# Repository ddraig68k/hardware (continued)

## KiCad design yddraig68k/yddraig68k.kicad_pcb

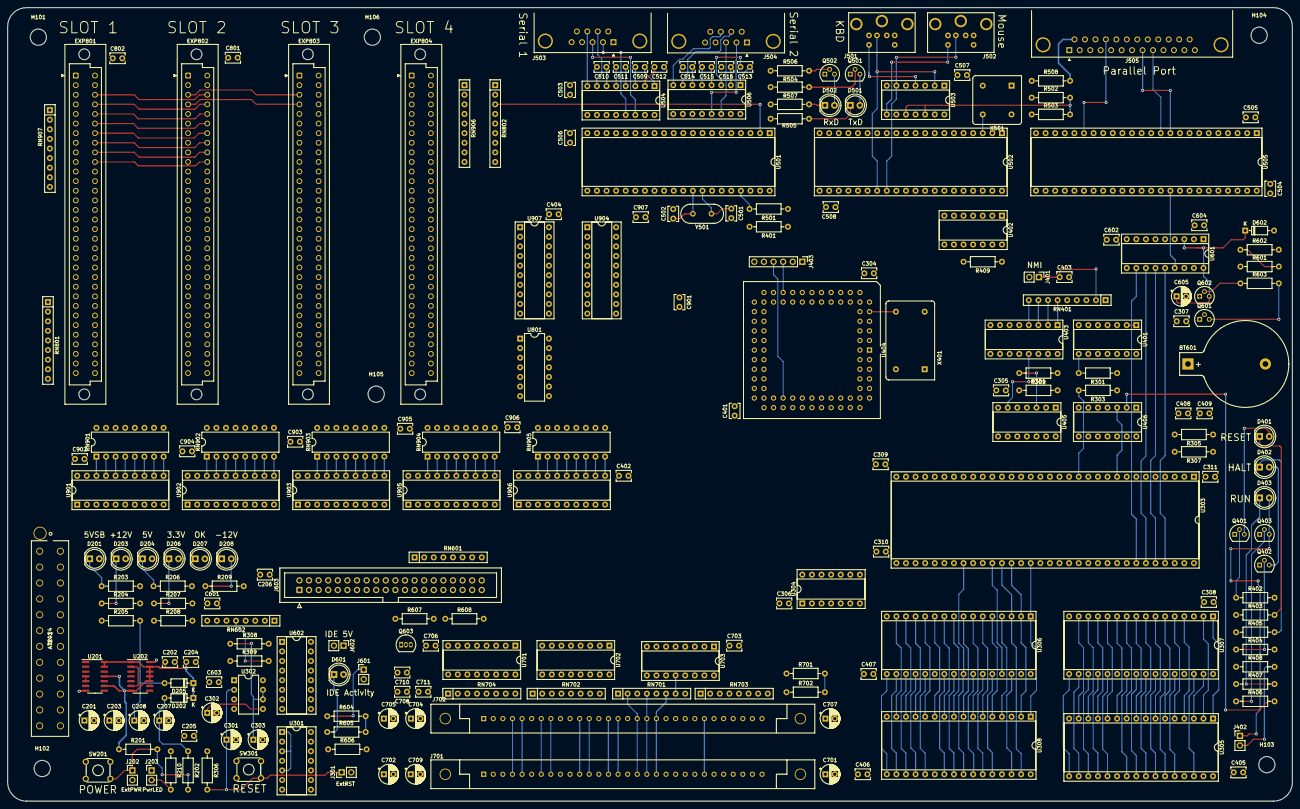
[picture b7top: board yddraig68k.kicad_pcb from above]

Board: 4 copper layers, 340.0 x 210.0 mm, 222 parts (0 on the bottom side), 370 nets.

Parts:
BT601: CR2032; BatteryHolder_Keystone_103_1x20mm
C201, C203, C701, C704, C707, C709: 47uF; CP_Radial_D5.0mm_P2.50mm
C202, C204, C205, C206, C304, C305, C306, C307, C308, C309, C310, C311, C401, C402, C403, C404, C405, C406, C407, C408, C409, C503, C504, C505, C506, C507, C508, C509, C510, C511, C512, C513, C514, C515, C516, C601, C602, C603, C604, C703, C706, C708, C710, C711, C801, C802, C901, C902, C903, C904, C905, C906, C907: 100nF; C_Disc_D3.8mm_W2.6mm_P2.50mm
C207: 1uF; CP_Radial_D5.0mm_P2.50mm
C208, C301, C605, C702, C705: 10uF; CP_Radial_D5.0mm_P2.50mm
C302, C303: 10nF; CP_Radial_D5.0mm_P2.50mm
C501: 10pF; C_Disc_D3.8mm_W2.6mm_P2.50mm
C502: 5pF; C_Disc_D3.8mm_W2.6mm_P2.50mm
D201, D203, D204, D206, D207, D208: LED; LED_D5.0mm
D202, D205, D602: 1N4148; D_DO-35_SOD27_P7.62mm_Horizontal
D401, D402: RED; LED_D5.0mm
D403: GREEN; LED_D5.0mm
D501, D502: Green; LED_D5.0mm
D601: Blue; LED_D5.0mm
EXP801, EXP802, EXP803, EXP804: D68K_64PIN_PCB; DIN41612_C_2x32_Female_Vertical_THT
H101, H102, H103, H104, H105, H106: MountingHole; MountingHole_4.3mm_M4
J201: ATX-24; 1-1775099-3
J202: ExtPWR; PinHeader_1x02_P2.54mm_Vertical
J203: PWRLED; PinHeader_1x02_P2.54mm_Vertical
J301: Conn_01x02; PinHeader_1x02_P2.54mm_Vertical
J401: NMI Reset; PinHeader_1x02_P2.54mm_Vertical
J402: Ext RUN LED; PinHeader_1x02_P2.54mm_Vertical
J403: Conn_01x06; PinHeader_1x06_P2.54mm_Vertical
J501: Keyboard; MINI-DIN-6-FULL-SHIELD
J502: Mouse; MINI-DIN-6-FULL-SHIELD
J503: Serial1; DSUB-9_Male_Horizontal_P2.77x2.84mm_EdgePinOffset4.94mm_Hou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
J504: Serial2; DSUB-9_Male_Horizontal_P2.77x2.84mm_EdgePinOffset4.94mm_Hou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
J505: Parallel; DSUB-25_Female_Horizontal_P2.77x2.84mm_EdgePinOffset7.70mm_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
J601: IDE LED; PinHeader_1x02_P2.54mm_Vertical
J602: IDE 5V; PinHeader_1x02_P2.54mm_Vertical
J603: IDE_Interface; IDC-Header_2x20_P2.54mm_Vertical
J701, J702: SIMM-30
Q401, Q402, Q403, Q501, Q502, Q602: 2N4403; TO-92
Q601: Q_NPN_EBC; TO-92
Q603: 2N7000; TO-92_Inline
R201, R205, R306, R502, R503, R607, R608: 10K; R_Axial_DIN0207_L6.3mm_D2.5mm_P10.16mm_Horizontal
R202: 470R; R_Axial_DIN0207_L6.3mm_D2.5mm_P10.16mm_Horizontal
R203, R206, R207, R208, R210, R604, R605: 330R; R_Axial_DIN0207_L6.3mm_D2.5mm_P10.16mm_Horizontal
R204, R209: 680R; R_Axial_DIN0207_L6.3mm_D2.5mm_P10.16mm_Horizontal
R301, R302, R303, R304, R305, R307, R309, R401, R409, R501, R601, R602, R603: 4K7; R_Axial_DIN0207_L6.3mm_D2.5mm_P10.16mm_Horizontal
R308: 38K; R_Axial_DIN0207_L6.3mm_D2.5mm_P10.16mm_Horizontal
R402, R404, R406, R508: 1K; R_Axial_DIN0207_L6.3mm_D2.5mm_P10.16mm_Horizontal
R403, R405, R407, R408, R504, R505, R506, R507: 150R; R_Axial_DIN0207_L6.3mm_D2.5mm_P10.16mm_Horizontal
R606: 1M; R_Axial_DIN0207_L6.3mm_D2.5mm_P10.16mm_Horizontal
R701, R702: 22R; R_Axial_DIN0207_L6.3mm_D2.5mm_P10.16mm_Horizontal
RN401, RN801, RN802, RN906, RN907: 10K; R_Array_SIP9
RN601, RN602, RN701, RN702, RN703, RN704: 22R; R_Array_SIP8
RN901, RN902, RN903, RN904, RN905: 22R; DIP-16_W7.62mm
SW201, SW301: SW_DPST; SW_TH_Tactile_Omron_B3F-10xx
U201, U202: 74HCT74; SO-14_3.9x8.65mm_P1.27mm
U301, U503: 74LS06; DIP-14_W7.62mm_Socket
U302: NE555P; DIP-8_W7.62mm
U303: 68000D; DIP-64_W22.86mm_Socket
U304: 74LS32; DIP-14_W7.62mm_Socket
U305, U306: SST39SF040; DIP-32_W15.24mm_Socket
U307, U308: AS6C4008-55PCN; DIP-32_W15.24mm_Socket
U401: 74HC164; DIP-14_W7.62mm_Socket
U402, U405: 74LS08; DIP-14_W7.62mm_Socket
U403: 74LS148; DIP-16_W7.62mm_Socket
U404: XC95108PC84; PLCC-84_THT-Socket
U406: 74LS04; DIP-14_W7.62mm_Socket
U501: 68681; DIP-40_W15.24mm_Socket
U502: VT82C42; DIP-40_W15.24mm_Socket
U504, U506: MAX202; DIP-16_W7.62mm_Socket
U505: 68230; DIP-48_W15.24mm_Socket
U601: RTC-72421; DIP-18_W7.62mm_Socket
U602: 74LS139; DIP-16_W7.62mm_Socket
U701, U702, U703: 74LS157; DIP-16_W7.62mm_Socket
U801: 74LS21; DIP-14_W7.62mm
U901, U902, U903: 74LS541; DIP-20_W7.62mm_Socket
U904, U905, U906, U907: 74LS245; DIP-20_W7.62mm_Socket
X401: 40MHz; Oscillator_DIP-14
X501: CXO_DIP8; Oscillator_DIP-8
Y501: 3.6864MHz; Crystal_HC18-U_Vertical

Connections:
+3V3: D206.2, EXP801.C30, EXP802.C30, EXP803.C30, EXP804.C30, J201.1, J201.2, J201.12, J201.13
+5V: C201.1, C203.1, C205.1, C206.1, C304.1, C305.1, C306.1, C307.1, C308.1, C309.1, C310.1, C311.1, C401.1, C402.1, C404.1, C405.1, C406.1, C407.1, C408.1, C409.1, C503.1, C504.1, C505.1, C506.1, C507.1, C508.1, C512.1, C516.2, C601.1, C602.1, C603.1, C604.1, C701.1, C702.1, C703.1, C704.1, C705.1, C706.1, C707.1, C708.1, C709.1, C710.1, C711.1, C801.1, C802.1, C901.1, C902.1, C903.1, C904.1, C905.1, C906.1, C907.1, D204.2, D601.2, EXP801.A1, EXP801.A24, EXP801.C1, EXP802.A1, EXP802.A24, EXP802.C1, EXP803.A1, EXP803.A24, EXP803.C1, EXP804.A1, EXP804.A24, EXP804.C1, J201.4, J201.6, J201.21, J201.22, J201.23, J203.1, J403.1, J501.4, J502.4, J601.2, J602.2, J701.1, J701.30, J702.1, J702.30, Q401.1, Q402.1, Q403.1, Q501.1, Q502.1, Q602.1, R301.1, R302.1, R303.1, R304.1, R305.1, R306.1, R307.1, R308.1, R309.1, R401.1, R409.1, R501.1, R502.1, R503.1, R508.1, R601.1, R606.1, R608.2, RN401.1, RN801.1, RN802.1, U301.9, U301.11, U301.13, U301.14, U302.4, U302.8, U303.14, U303.49, U304.14, U305.32, U306.32, U307.32, U308.32, U401.14, U402.14, U403.16, U404.22, U404.38, U404.64, U404.73, U404.78, U405.14, U406.14, U501.40, U502.5, U502.25, U502.26, U502.40, U503.14, U504.16, U505.12, U506.16, U602.13, U602.14, U602.15, U602.16, U701.16, U702.16, U703.16, U801.14, U901.20, U902.20, U903.20, U904.20, U905.20, U906.20, U907.20, X401.14, X501.1, X501.8
+5V_SB: C202.1, C204.1, D201.2, D202.1, D205.1, EXP801.C2, EXP802.C2, EXP803.C2, EXP804.C2, J201.9, R201.1, R205.1, U201.9, U201.11, U201.13, U201.14, U202.1, U202.7, U202.10, U202.11, U202.12, U202.13
+12V: D203.2, EXP801.A31, EXP801.C31, EXP802.A31, EXP802.C31, EXP803.A31, EXP803.C31, EXP804.A31, EXP804.C31, J201.10, J201.11
-12V: D208.1, EXP801.A30, EXP802.A30, EXP803.A30, EXP804.A30, J201.14
/CPU, RAM and ROM/A1: RN601.1, U303.29, U305.12, U306.12, U307.12, U308.12, U501.1, U502.9, U505.29, U601.4, U701.2, U901.2
/CPU, RAM and ROM/A2: RN601.3, U303.30, U305.11, U306.11, U307.11, U308.11, U501.3, U505.28, U601.5, U701.3, U901.3
/CPU, RAM and ROM/A3: RN601.5, U303.31, U305.10, U306.10, U307.10, U308.10, U501.5, U505.27, U601.6, U701.5, U901.4
/CPU, RAM and ROM/A4: U303.32, U305.9, U306.9, U307.9, U308.9, U501.6, U505.26, U601.7, U701.6, U901.5
/CPU, RAM and ROM/A5: U303.33, U305.8, U306.8, U307.8, U308.8, U505.25, U701.11, U901.6
/CPU, RAM and ROM/A6: U303.34, U305.7, U306.7, U307.7, U308.7, U701.10, U901.7
/CPU, RAM and ROM/A7: U303.35, U305.6, U306.6, U307.6, U308.6, U602.2, U701.14, U901.8
/CPU, RAM and ROM/A8: U303.36, U305.5, U306.5, U307.5, U308.5, U404.71, U701.13, U901.9
/CPU, RAM and ROM/A9: U303.37, U305.27, U306.27, U307.27, U308.27, U404.72, U702.2, U902.2
/CPU, RAM and ROM/A10: U303.38, U305.26, U306.26, U307.26, U308.26, U404.74, U702.3, U902.3
/CPU, RAM and ROM/A11: U303.39, U305.23, U306.23, U307.23, U308.23, U404.75, U702.5, U902.4
/CPU, RAM and ROM/A12: U303.40, U305.25, U306.25, U307.25, U308.25, U404.76, U702.6, U902.5
/CPU, RAM and ROM/A13: U303.41, U305.4, U306.4, U307.4, U308.4, U404.77, U702.11, U902.6
/CPU, RAM and ROM/A14: U303.42, U305.28, U306.28, U307.28, U308.28, U404.79, U702.10, U902.7
/CPU, RAM and ROM/A15: U303.43, U305.29, U306.29, U307.3, U308.3, U404.80, U702.14, U902.8
/CPU, RAM and ROM/A16: U303.44, U305.3, U306.3, U307.31, U308.31, U404.81, U702.13, U902.9
/CPU, RAM and ROM/A17: U303.45, U305.2, U306.2, U307.2, U308.2, U404.82, U703.2, U903.2
/CPU, RAM and ROM/A18: U303.46, U305.30, U306.30, U307.30, U308.30, U404.83, U703.3, U903.3
/CPU, RAM and ROM/A19: U303.47, U305.1, U306.1, U307.1, U308.1, U404.84, U703.5, U903.4
/CPU, RAM and ROM/A20: U303.48, U404.57, U703.6
/CPU, RAM and ROM/A21: U303.50, U404.58, U703.11
/CPU, RAM and ROM/A22: U303.51, U404.61, U703.10
/CPU, RAM and ROM/A23: U303.52, U404.62, U703.14
/CPU, RAM and ROM/CLK10: U303.15, U404.10, U505.40, U904.11
/CPU, RAM and ROM/D0: J603.4, J702.3, U303.5, U305.13, U307.13, U905.2
/CPU, RAM and ROM/D1: J603.6, J702.6, U303.4, U305.14, U307.14, U905.3
/CPU, RAM and ROM/D2: J603.8, J702.10, U303.3, U305.15, U307.15, U905.4
/CPU, RAM and ROM/D3: J603.10, J702.13, U303.2, U305.17, U307.17, U905.5
/CPU, RAM and ROM/D4: J603.12, J702.16, U303.1, U305.18, U307.18, U905.6
/CPU, RAM and ROM/D5: J603.14, J702.20, U303.64, U305.19, U307.19, U905.7
/CPU, RAM and ROM/D6: J603.16, J702.23, U303.63, U305.20, U307.20, U905.8
/CPU, RAM and ROM/D7: J603.18, J702.25, U303.62, U305.21, U307.21, U905.9
/CPU, RAM and ROM/D8: J603.17, J701.3, U303.61, U306.13, U308.13, U501.25, U502.12, U505.44, U601.14, U906.2
/CPU, RAM and ROM/D9: J603.15, J701.6, U303.60, U306.14, U308.14, U501.16, U502.13, U505.45, U601.13, U906.3
/CPU, RAM and ROM/D10: J603.13, J701.10, U303.59, U306.15, U308.15, U501.24, U502.14, U505.46, U601.12, U906.4
/CPU, RAM and ROM/D11: J603.11, J701.13, U303.58, U306.17, U308.17, U501.17, U502.15, U505.47, U601.11, U906.5
/CPU, RAM and ROM/D12: J603.9, J701.16, U303.57, U306.18, U308.18, U501.23, U502.16, U505.48, U906.6
/CPU, RAM and ROM/D13: J603.7, J701.20, U303.56, U306.19, U308.19, U501.18, U502.17, U505.1, U906.7
/CPU, RAM and ROM/D14: J603.5, J701.23, U303.55, U306.20, U308.20, U501.22, U502.18, U505.2, U906.8
/CPU, RAM and ROM/D15: J603.3, J701.25, U303.54, U306.21, U308.21, U501.19, U502.19, U505.3, U906.9
/CPU, RAM and ROM/E: U303.20, U904.12
/CPU, RAM and ROM/FC0: U303.28, U404.11
/CPU, RAM and ROM/FC1: U303.27, U404.12
/CPU, RAM and ROM/FC2: U303.26, U404.13
/CPU, RAM and ROM/RD~WR: U303.9, U305.31, U306.31, U307.29, U308.29, U404.66, U406.3, U501.8, U502.10, U505.43, U601.10, U904.15
/CPU, RAM and ROM/RESET: U301.1, U301.3, U301.5, U302.3
/CPU, RAM and ROM/~AS: R301.2, U303.6, U401.8, U404.63, U901.1, U902.1, U903.1, U904.14
/CPU, RAM and ROM/~BERR: U303.22, U402.8
/CPU, RAM and ROM/~CPU_RESET: R307.2, R402.2, U301.6, U303.18, U402.13
/CPU, RAM and ROM/~CS_ROM: U304.2, U304.10, U404.7
/CPU, RAM and ROM/~CS_SRAM: U304.5, U304.13, U404.6
/CPU, RAM and ROM/~DTACK: U303.10, U402.6
/CPU, RAM and ROM/~HALT: R305.2, R404.2, U301.4, U303.17, U402.12
/CPU, RAM and ROM/~IPL0: U303.25, U403.9
/CPU, RAM and ROM/~IPL1: U303.24, U403.7
/CPU, RAM and ROM/~IPL2: U303.23, U403.6
/CPU, RAM and ROM/~LDS: U303.8, U304.1, U304.4, U404.65, U904.17
/CPU, RAM and ROM/~RD~WR: U305.24, U306.24, U307.24, U308.24, U406.4, U502.8, U601.8, U905.1, U906.1
/CPU, RAM and ROM/~RESET: R309.2, RN602.5, U301.2, U401.9, U404.48, U501.34, U502.4, U505.39, U601.15, U904.18
/CPU, RAM and ROM/~UDS: U303.7, U304.9, U304.12, U404.44, U904.16
/CPU, RAM and ROM/~VMA: U303.19, U904.13
/CPU, RAM and ROM/~VPA: R302.2, U303.21, U405.3
/DRAM Interface/DRAM_MUX: U404.50, U701.1, U702.1, U703.1
/DRAM Interface/~CAS0: RN703.1, U404.55
/DRAM Interface/~CAS1: RN703.3, U404.56
/DRAM Interface/~DRAM_WE: R701.2, R702.2, U404.51
/DRAM Interface/~RAS0: RN703.5, U404.53
/DRAM Interface/~RAS1: RN703.7, U404.45
/Decode and Logic/BOOTROM: U401.6, U404.1
/Decode and Logic/~CPLD_BERR: U402.9, U404.69
/Decode and Logic/~CPLD_VPA: U404.39, U405.1
/Decode and Logic/~CS_DUART: U404.15, U501.35
/Decode and Logic/~CS_EXTDATA1: U404.23, U907.14
/Decode and Logic/~CS_EXTDATA2: U404.24, U907.13
/Decode and Logic/~CS_EXTDATA3: U404.25, U907.12
/Decode and Logic/~CS_EXTDATA4: U404.26, U907.11
/Decode and Logic/~CS_EXTREG1: U404.31, U907.18
/Decode and Logic/~CS_EXTREG2: U404.32, U907.17
/Decode and Logic/~CS_EXTREG3: U404.33, U907.16
/Decode and Logic/~CS_EXTREG4: U404.34, U907.15
/Decode and Logic/~CS_IDE: U404.35, U602.1
/Decode and Logic/~CS_KBD: U404.5, U502.6
/Decode and Logic/~CS_PIT: U404.4, U505.41
/Decode and Logic/~CS_RTC: U404.20, U601.2
/Decode and Logic/~DATCK_68K: R409.2, U402.1, U501.9, U505.42
/Decode and Logic/~DATCK_EXT: U402.5, U801.8
/Decode and Logic/~DTACK_CPLD: U402.2, U404.2
/Decode and Logic/~EXTINT1: EXP801.A28, RN401.3, U403.11
/Decode and Logic/~EXTINT2: EXP802.A28, RN401.8, U403.3
/Decode and Logic/~EXTINT3: EXP803.A28, RN401.9, U403.4
/Decode and Logic/~EXT_BERR: U402.10, U801.6
/Decode and Logic/~EXT_LDS: U404.68, U905.19
/Decode and Logic/~EXT_UDS: U404.70, U906.19
/Decode and Logic/~EXT_VPA: EXP801.A23, EXP802.A23, EXP803.A23, EXP804.A23, RN802.6, U405.2
/Decode and Logic/~IDE_RD: RN602.3, U404.18
/Decode and Logic/~IDE_WR: RN602.1, U404.17
/Decode and Logic/~INT_DUART: RN401.6, U403.1, U501.21
/Decode and Logic/~INT_IDE: Q603.3, R606.2, RN401.4, U403.12
/Decode and Logic/~INT_PIT0: U405.4, U505.33
/Decode and Logic/~INT_PIT1: U405.5, U505.35
/Decode and Logic/~INT_PS2: R502.2, R503.2, RN401.7, U403.2, U503.10, U503.12
/Decode and Logic/~RUN: R406.2, U406.2
/Expansion Bus/BA1: EXP801.A12, EXP802.A12, EXP803.A12, EXP804.A12, RN901.16
/Expansion Bus/BA2: EXP801.C12, EXP802.C12, EXP803.C12, EXP804.C12, RN901.15
/Expansion Bus/BA3: EXP801.A13, EXP802.A13, EXP803.A13, EXP804.A13, RN901.14
/Expansion Bus/BA4: EXP801.C13, EXP802.C13, EXP803.C13, EXP804.C13, RN901.13
/Expansion Bus/BA5: EXP801.A14, EXP802.A14, EXP803.A14, EXP804.A14, RN901.12
/Expansion Bus/BA6: EXP801.C14, EXP802.C14, EXP803.C14, EXP804.C14, RN901.11
/Expansion Bus/BA7: EXP801.A15, EXP802.A15, EXP803.A15, EXP804.A15, RN901.10
/Expansion Bus/BA8: EXP801.C15, EXP802.C15, EXP803.C15, EXP804.C15, RN901.9
/Expansion Bus/BA9: EXP801.A16, EXP802.A16, EXP803.A16, EXP804.A16, RN902.16
/Expansion Bus/BA10: EXP801.C16, EXP802.C16, EXP803.C16, EXP804.C16, RN902.15
/Expansion Bus/BA11: EXP801.A17, EXP802.A17, EXP803.A17, EXP804.A17, RN902.14
/Expansion Bus/BA12: EXP801.C17, EXP802.C17, EXP803.C17, EXP804.C17, RN902.13
/Expansion Bus/BA13: EXP801.A18, EXP802.A18, EXP803.A18, EXP804.A18, RN902.12
/Expansion Bus/BA14: EXP801.C18, EXP802.C18, EXP803.C18, EXP804.C18, RN902.11
/Expansion Bus/BA15: EXP801.A19, EXP802.A19, EXP803.A19, EXP804.A19, RN902.10
/Expansion Bus/BA16: EXP801.C19, EXP802.C19, EXP803.C19, EXP804.C19, RN902.9
/Expansion Bus/BA17: EXP801.A20, EXP802.A20, EXP803.A20, EXP804.A20, RN903.16
/Expansion Bus/BA18: EXP801.C20, EXP802.C20, EXP803.C20, EXP804.C20, RN903.15
/Expansion Bus/BA19: EXP801.A21, EXP802.A21, EXP803.A21, EXP804.A21, RN903.14
/Expansion Bus/BCLK10: EXP801.C23, EXP802.C23, EXP803.C23, EXP804.C23, U904.9
/Expansion Bus/BD0: EXP801.A3, EXP802.A3, EXP803.A3, EXP804.A3, RN904.16, RN906.2
/Expansion Bus/BD1: EXP801.C3, EXP802.C3, EXP803.C3, EXP804.C3, RN904.15, RN906.3
/Expansion Bus/BD2: EXP801.A4, EXP802.A4, EXP803.A4, EXP804.A4, RN904.14, RN906.4
/Expansion Bus/BD3: EXP801.C4, EXP802.C4, EXP803.C4, EXP804.C4, RN904.13, RN906.5
/Expansion Bus/BD4: EXP801.A5, EXP802.A5, EXP803.A5, EXP804.A5, RN904.12, RN906.6
/Expansion Bus/BD5: EXP801.C5, EXP802.C5, EXP803.C5, EXP804.C5, RN904.11, RN906.7
/Expansion Bus/BD6: EXP801.A6, EXP802.A6, EXP803.A6, EXP804.A6, RN904.10, RN906.8
/Expansion Bus/BD7: EXP801.C6, EXP802.C6, EXP803.C6, EXP804.C6, RN904.9, RN906.9
/Expansion Bus/BD8: EXP801.A7, EXP802.A7, EXP803.A7, EXP804.A7, RN905.16, RN907.2
/Expansion Bus/BD9: EXP801.C7, EXP802.C7, EXP803.C7, EXP804.C7, RN905.15, RN907.3
/Expansion Bus/BD10: EXP801.A8, EXP802.A8, EXP803.A8, EXP804.A8, RN905.14, RN907.4
/Expansion Bus/BD11: EXP801.C8, EXP802.C8, EXP803.C8, EXP804.C8, RN905.13, RN907.5
/Expansion Bus/BD12: EXP801.A9, EXP802.A9, EXP803.A9, EXP804.A9, RN905.12, RN907.6
/Expansion Bus/BD13: EXP801.C9, EXP802.C9, EXP803.C9, EXP804.C9, RN905.11, RN907.7
/Expansion Bus/BD14: EXP801.A10, EXP802.A10, EXP803.A10, EXP804.A10, RN905.10, RN907.8
/Expansion Bus/BD15: EXP801.C10, EXP802.C10, EXP803.C10, EXP804.C10, RN905.9, RN907.9
/Expansion Bus/BE: EXP801.C21, EXP802.C21, EXP803.C21, EXP804.C21, U904.8
/Expansion Bus/BRD~WR: EXP801.A26, EXP802.A26, EXP803.A26, EXP804.A26, U904.5
/Expansion Bus/~BAS: EXP801.A22, EXP802.A22, EXP803.A22, EXP804.A22, U904.6
/Expansion Bus/~BCS_EXTDATA1: EXP801.C27, U907.6
/Expansion Bus/~BCS_EXTDATA2: EXP802.C27, U907.7
/Expansion Bus/~BCS_EXTDATA3: EXP803.C27, U907.8
/Expansion Bus/~BCS_EXTDATA4: EXP804.C27, U907.9
/Expansion Bus/~BCS_EXTREG1: EXP801.A27, U907.2
/Expansion Bus/~BCS_EXTREG2: EXP802.A27, U907.3
/Expansion Bus/~BCS_EXTREG3: EXP803.A27, U907.4
/Expansion Bus/~BCS_EXTREG4: EXP804.A27, U907.5
/Expansion Bus/~BLDS: EXP801.A25, EXP802.A25, EXP803.A25, EXP804.A25, U904.3
/Expansion Bus/~BRESET: EXP801.C26, EXP802.C26, EXP803.C26, EXP804.C26, U904.2
/Expansion Bus/~BUDS: EXP801.C25, EXP802.C25, EXP803.C25, EXP804.C25, U904.4
/Expansion Bus/~BVMA: EXP801.C22, EXP802.C22, EXP803.C22, EXP804.C22, U904.7
/Expansion Bus/~DTACK_EXT1: EXP801.C28, RN801.5, U801.9
/Expansion Bus/~DTACK_EXT2: EXP802.C28, RN801.4, U801.10
/Expansion Bus/~DTACK_EXT3: EXP803.C28, RN801.3, U801.12
/Expansion Bus/~DTACK_EXT4: EXP804.A28, RN801.2, U801.13
/Expansion Bus/~EXT_BERR1: EXP801.A29, RN801.9, U801.1
/Expansion Bus/~EXT_BERR2: EXP802.A29, RN801.8, U801.2
/Expansion Bus/~EXT_BERR3: EXP803.A29, RN801.7, U801.4
/Expansion Bus/~EXT_BERR4: EXP804.A29, RN801.6, U801.5
/Expansion Bus/~EXT_PD1: EXP801.C29, RN802.2, U501.36
/Expansion Bus/~EXT_PD2: EXP802.C29, RN802.3, U501.2
/Expansion Bus/~EXT_PD3: EXP803.C29, RN802.4, U501.39
/Expansion Bus/~EXT_PD4: EXP804.C29, RN802.5, U501.38
/IDE Interface/ACTIVE: J603.39, R604.2, R605.2
/IDE Interface/IRQ: J603.31, Q603.2
/Peripherals/PPACK: J505.10, U505.13
/Peripherals/PPBUSY: J505.11, U505.17
/Peripherals/PPERROR: J505.15, U505.15
/Peripherals/PPINIT: J505.16, U505.16
/Peripherals/PPPAPER: J505.12, U505.18
/Peripherals/PPSELECT: J505.17, U505.19
/Peripherals/PPSTROBE: J505.1, U505.14
/Peripherals/RXDA: R506.2, U501.31, U504.12
/Peripherals/TXDA: R504.2, U501.30, U504.11
/Power/PWR_OK: D207.2, J201.8
/Power/~PWR_ON: J201.16, U202.5
GND: BT601.2, C201.2, C202.2, C203.2, C204.2, C205.2, C206.2, C207.2, C208.2, C301.2, C302.2, C303.2, C304.2, C305.2, C306.2, C307.2, C308.2, C309.2, C310.2, C311.2, C401.2, C402.2, C403.2, C404.2, C405.2, C406.2, C407.2, C408.2, C409.2, C501.2, C502.2, C503.2, C504.2, C505.2, C506.2, C507.2, C508.2, C510.2, C514.2, C601.2, C602.2, C603.2, C604.2, C605.2, C701.2, C702.2, C703.2, C704.2, C705.2, C706.2, C707.2, C708.2, C709.2, C710.2, C711.2, C801.2, C802.2, C901.2, C902.2, C903.2, C904.2, C905.2, C906.2, C907.2, EXP801.A2, EXP801.A11, EXP801.A32, EXP801.C11, EXP801.C24, EXP801.C32, EXP802.A2, EXP802.A11, EXP802.A32, EXP802.C11, EXP802.C24, EXP802.C32, EXP803.A2, EXP803.A11, EXP803.A32, EXP803.C11, EXP803.C24, EXP803.C32, EXP804.A2, EXP804.A11, EXP804.A32, EXP804.C11, EXP804.C24, EXP804.C32, J201.3, J201.5, J201.7, J201.15, J201.17, J201.18, J201.19, J201.24, J202.2, J301.2, J401.2, J403.6, J501.3, J501.7, J502.3, J502.7, J503.0, J503.5, J504.0, J504.5, J505.0, J505.18, J505.19, J505.20, J505.21, J505.22, J505.23, J505.24, J505.25, J603.2, J603.19, J603.22, J603.24, J603.26, J603.28, J603.30, J603.40, J701.9, J701.22, J702.9, J702.22, Q601.1, Q603.1, R203.2, R204.2, R206.2, R207.2, R208.2, R209.2, R210.2, R403.1, R405.1, R407.1, R408.1, R505.2, R507.2, R602.2, R607.2, RN906.1, RN907.1, SW201.1, SW201.3, SW301.1, SW301.3, U201.7, U202.14, U301.7, U302.1, U303.16, U303.53, U304.7, U305.16, U306.16, U307.16, U308.16, U401.7, U402.7, U403.5, U403.8, U404.8, U404.16, U404.27, U404.42, U404.49, U404.60, U405.7, U405.9, U405.10, U405.12, U405.13, U406.5, U406.7, U406.9, U406.11, U406.13, U501.20, U502.2, U502.7, U502.20, U503.7, U504.15, U505.38, U506.15, U601.9, U602.3, U602.8, U701.8, U701.15, U702.8, U702.15, U703.8, U703.13, U703.15, U801.7, U901.10, U901.19, U902.10, U902.19, U903.5, U903.6, U903.7, U903.8, U903.9, U903.10, U903.19, U904.1, U904.10, U904.19, U905.10, U906.10, U907.1, U907.10, U907.19, X401.7, X501.4
unnamed: BT601.1, D602.2
unnamed: C207.1, D202.2, R202.1, U201.1
unnamed: C208.1, D205.2, R205.2, U201.3
unnamed: C301.1, J301.1, R306.2, SW301.2, SW301.4, U302.2
unnamed: C302.1, U302.5
unnamed: C303.1, R308.2, U302.6, U302.7
unnamed: C403.1, J401.1, RN401.2, U403.10
unnamed: C501.1, U501.33, Y501.1
unnamed: C502.1, U501.32, Y501.2
unnamed: C509.1, U504.1
unnamed: C509.2, U504.3
unnamed: C510.1, U504.6
unnamed: C511.1, U504.4
unnamed: C511.2, U504.5
unnamed: C512.2, U504.2
unnamed: C513.1, U506.1
unnamed: C513.2, U506.3
unnamed: C514.1, U506.6
unnamed: C515.1, U506.4
unnamed: C515.2, U506.5
unnamed: C516.1, U506.2
unnamed: C605.1, D602.1, Q602.3, U601.3, U601.18
unnamed: D201.1, R203.1
unnamed: D203.1, R204.1
unnamed: D204.1, R206.1
unnamed: D206.1, R207.1
unnamed: D207.1, R208.1
unnamed: D208.2, R209.1
unnamed: D401.1, R403.2
unnamed: D401.2, Q401.3
unnamed: D402.1, R405.2
unnamed: D402.2, Q402.3
unnamed: D403.1, R407.2
unnamed: D403.2, J402.1, Q403.3
unnamed: D501.1, R505.1
unnamed: D501.2, Q501.3
unnamed: D502.1, R507.1
unnamed: D502.2, Q502.3
unnamed: D601.1, R605.1
unnamed: J202.1, R201.2, R202.2, SW201.2, SW201.4
unnamed: J203.2, R210.1
unnamed: J402.2, R408.2
unnamed: J403.2, U404.30
unnamed: J403.3, U404.28
unnamed: J403.4, U404.59
unnamed: J403.5, U404.29
unnamed: J501.1, U502.27, U503.2
unnamed: J501.5, U502.1, U503.4
unnamed: J502.1, U502.28, U503.6
unnamed: J502.5, U502.39, U503.8
unnamed: J503.2, U504.13
unnamed: J503.3, U504.14
unnamed: J503.7, U504.7
unnamed: J503.8, U504.8
unnamed: J504.2, U506.13
unnamed: J504.3, U506.14
unnamed: J504.7, U506.7
unnamed: J504.8, U506.8
unnamed: J505.2, U505.4
unnamed: J505.3, U505.5
unnamed: J505.4, U505.6
unnamed: J505.5, U505.7
unnamed: J505.6, U505.8
unnamed: J505.7, U505.9
unnamed: J505.8, U505.10
unnamed: J505.9, U505.11
unnamed: J505.14, R508.2
unnamed: J601.1, R604.1
unnamed: J602.1, J603.20
unnamed: J603.1, RN602.6
unnamed: J603.21, R607.1
unnamed: J603.23, RN602.2
unnamed: J603.25, RN602.4
unnamed: J603.29, R608.1
unnamed: J603.33, RN601.4
unnamed: J603.35, RN601.2
unnamed: J603.36, RN601.6
unnamed: J603.37, U602.4
unnamed: J603.38, U602.5
unnamed: J701.2, RN703.2
unnamed: J701.4, J702.4, RN704.2
unnamed: J701.5, J702.5, RN704.4
unnamed: J701.7, J702.7, RN704.6
unnamed: J701.8, J702.8, RN704.8
unnamed: J701.11, J702.11, RN702.2
unnamed: J701.12, J702.12, RN702.4
unnamed: J701.14, J702.14, RN702.6
unnamed: J701.15, J702.15, RN702.8
unnamed: J701.17, J702.17, RN701.2
unnamed: J701.18, J702.18, RN701.4
unnamed: J701.19, J702.19, RN701.6
unnamed: J701.21, R701.1
unnamed: J701.24, J702.24, RN701.8
unnamed: J701.27, RN703.6
unnamed: J702.2, RN703.4
unnamed: J702.21, R702.1
unnamed: J702.27, RN703.8
unnamed: Q401.2, R402.1
unnamed: Q402.2, R404.1
unnamed: Q403.2, R406.1
unnamed: Q501.2, R504.1
unnamed: Q502.2, R506.1
unnamed: Q601.2, R601.2, R602.1
unnamed: Q601.3, R603.2
unnamed: Q602.2, R603.1
unnamed: R303.2, U303.13
unnamed: R304.2, U303.12
unnamed: R401.2, U401.1, U401.2
unnamed: R501.2, U501.37
unnamed: RN401.5, U403.13, U405.6
unnamed: RN701.1, U703.4
unnamed: RN701.3, U703.7
unnamed: RN701.5, U703.9
unnamed: RN701.7, U703.12
unnamed: RN702.1, U702.4
unnamed: RN702.3, U702.7
unnamed: RN702.5, U702.9
unnamed: RN702.7, U702.12
unnamed: RN704.1, U701.4
unnamed: RN704.3, U701.7
unnamed: RN704.5, U701.9
unnamed: RN704.7, U701.12
unnamed: RN901.1, U901.18
unnamed: RN901.2, U901.17
unnamed: RN901.3, U901.16
unnamed: RN901.4, U901.15
unnamed: RN901.5, U901.14
unnamed: RN901.6, U901.13
unnamed: RN901.7, U901.12
unnamed: RN901.8, U901.11
unnamed: RN902.1, U902.18
unnamed: RN902.2, U902.17
unnamed: RN902.3, U902.16
unnamed: RN902.4, U902.15
unnamed: RN902.5, U902.14
unnamed: RN902.6, U902.13
unnamed: RN902.7, U902.12
unnamed: RN902.8, U902.11
unnamed: RN903.1, U903.18
unnamed: RN903.2, U903.17
unnamed: RN903.3, U903.16
unnamed: RN903.4, U903.15
unnamed: RN903.5, U903.14
unnamed: RN903.6, U903.13
unnamed: RN903.7, U903.12
unnamed: RN903.8, U903.11
unnamed: RN904.1, U905.18
unnamed: RN904.2, U905.17
unnamed: RN904.3, U905.16
unnamed: RN904.4, U905.15
unnamed: RN904.5, U905.14
unnamed: RN904.6, U905.13
unnamed: RN904.7, U905.12
unnamed: RN904.8, U905.11
unnamed: RN905.1, U906.18
unnamed: RN905.2, U906.17
unnamed: RN905.3, U906.16
unnamed: RN905.4, U906.15
unnamed: RN905.5, U906.14
unnamed: RN905.6, U906.13
unnamed: RN905.7, U906.12
unnamed: RN905.8, U906.11
unnamed: U201.2, U202.3
unnamed: U201.4, U201.5
unnamed: U201.6, U202.4
unnamed: U202.2, U202.6
unnamed: U304.3, U305.22
unnamed: U304.6, U307.22
unnamed: U304.8, U306.22
unnamed: U304.11, U308.22
unnamed: U402.3, U402.4
unnamed: U402.11, U406.1
unnamed: U404.9, X401.8
unnamed: U501.4, U506.9
unnamed: U501.7, U504.9
unnamed: U501.10, U506.12
unnamed: U501.11, U506.11
unnamed: U501.12, U506.10
unnamed: U501.29, U504.10
unnamed: U502.3, X501.5
unnamed: U502.23, U503.5
unnamed: U502.24, U503.9
unnamed: U502.35, U503.11
unnamed: U502.36, U503.13
unnamed: U502.37, U503.3
unnamed: U502.38, U503.1
